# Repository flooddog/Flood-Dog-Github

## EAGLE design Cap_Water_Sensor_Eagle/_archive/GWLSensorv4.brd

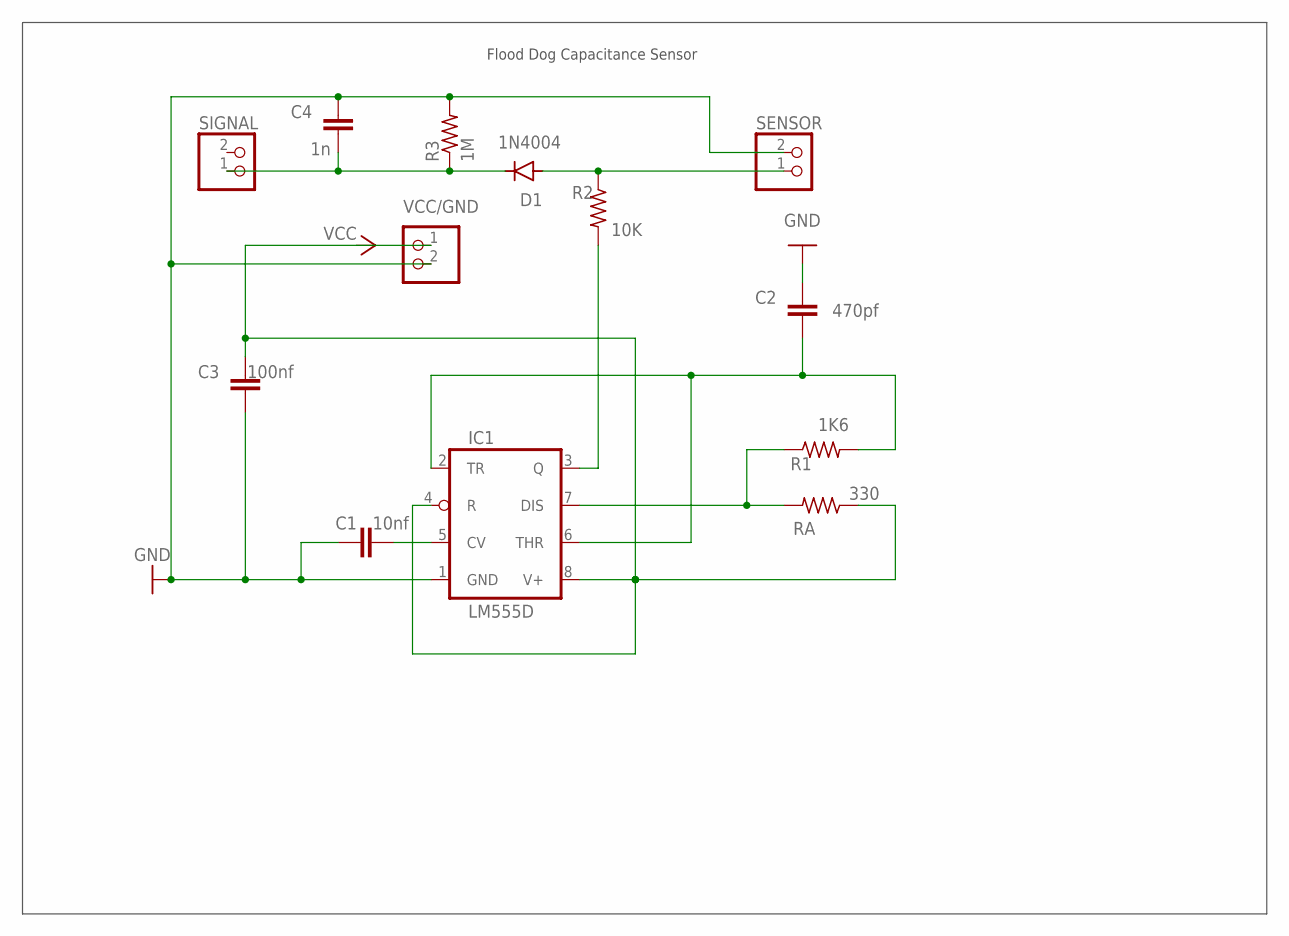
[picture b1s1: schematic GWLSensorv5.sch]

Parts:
C1: 10nf; C0805
C2: 470pf; C0805
C3: 100nf; C0805
C4: 1n; C0805
D1: 1N4004; DO41-10
IC1: LM555D; SO08
R1: 1K6; R0805
R2: 10K; R0805
R3: 1M; R0805
RA: 330; R0805
SENSOR: JST_2PIN-SMT; JST-PH-2-SMT
SIGNAL: JST_2PIN-SMT; JST-PH-2-SMT
VCC/GND: JST_2PIN-SMT; JST-PH-2-SMT

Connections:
GND: C1.1, C2.2, C3.1, C4.2, IC1.1 (GND), R3.2, SENSOR.2 (1), VCC/GND.2 (1)
unnamed: C4.1, D1.C, R3.1, SIGNAL.1 (2)
unnamed: IC1.7 (DIS), R1.1, RA.2
unnamed: C2.1, IC1.2 (TR), IC1.6 (THR), R1.2
unnamed: C1.2, IC1.5 (CV)
unnamed: D1.A, R2.1, SENSOR.1 (2)
unnamed: IC1.3 (Q), R2.2
VCC: C3.2, IC1.4 (R), IC1.8 (V+), RA.1, VCC/GND.1 (2)

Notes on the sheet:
Flood Dog Capacitance Sensor

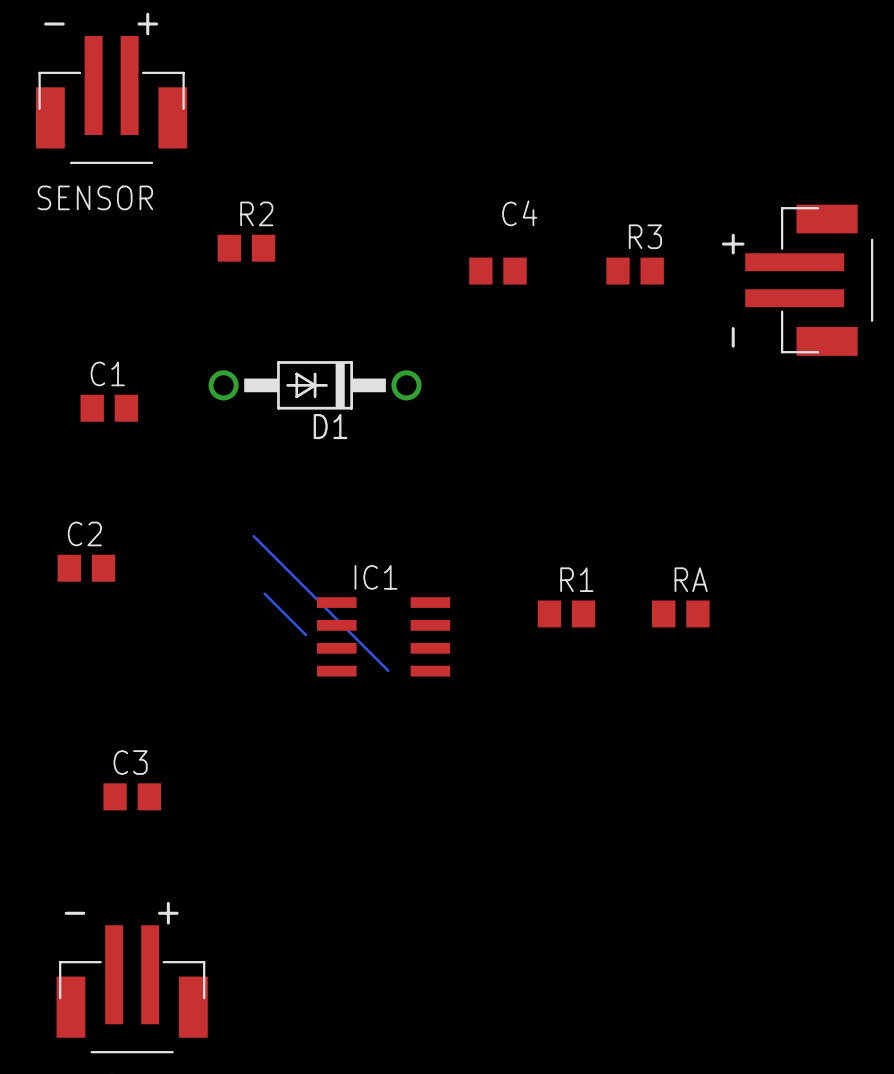
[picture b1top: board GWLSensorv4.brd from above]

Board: 2 copper layers, 13 parts (0 on the bottom side), 8 nets.

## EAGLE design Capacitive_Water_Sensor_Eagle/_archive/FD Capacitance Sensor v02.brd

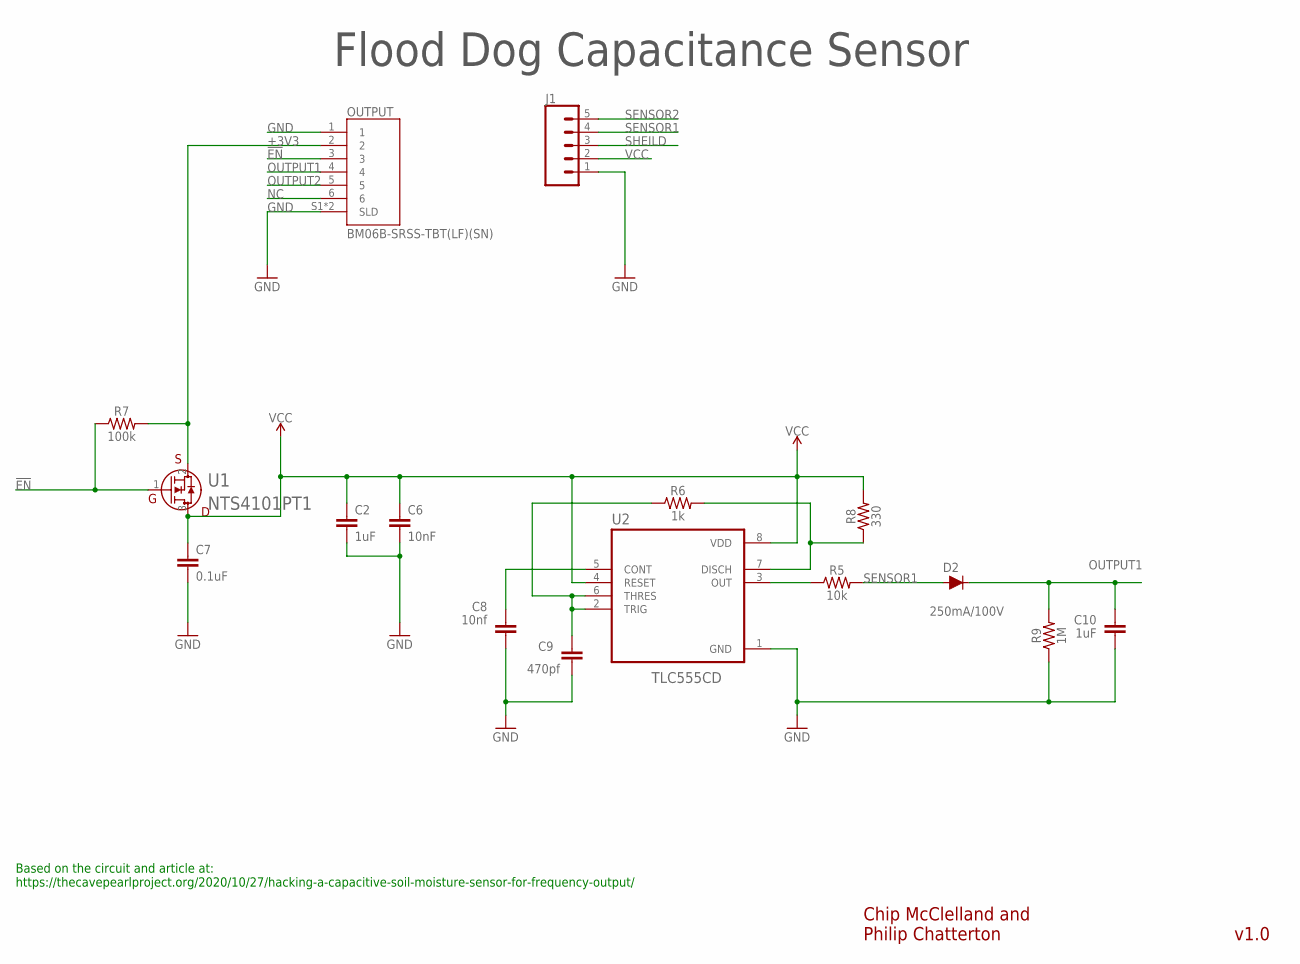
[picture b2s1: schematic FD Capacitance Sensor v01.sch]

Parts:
C2: 1uF; 0805@1
C6: 10nF; 0805@1
C7: 0.1uF; 0805@1
C8: 10nf; C0805
C9: 470pf; C0805
C10: 1uF; C0805
D2: 250mA/100V; SOD-323
J1: CONN_05SCREW; SCREWTERMINAL-3.5MM-5
OUTPUT: BM06B-SRSS-TBT(LF)(SN); JST_BM06B-SRSS-TB(LF)(SN)
R5: 10k; 0805
R6: 1k; 0805
R7: 100k; 0805; MPN MF-RES-0805-100K
R8: 330; 0805
R9: 1M; 0805
U1: NTS4101PT1; SOT_101PT1_ONS
U2: TLC555CD; SOIC127P599X175-8N

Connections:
!EN: OUTPUT.3, R7.1, U1.1 (G)
+3V3: OUTPUT.2, R7.2, U1.2 (S)
GND: C2.2, C6.2, C7.2, C8.1, C9.1, C10.1, J1.1, OUTPUT.1, OUTPUT.S1 (SLD), OUTPUT.S2 (SLD), R9.1, U2.1 (GND)
unnamed: C8.2, U2.5 (CONT)
unnamed: R5.1, U2.3 (OUT)
unnamed: C9.2, R6.1, U2.2 (TRIG), U2.6 (THRES)
unnamed: R6.2, R8.1, U2.7 (DISCH)
NC: OUTPUT.6
OUTPUT1: C10.2, D2.C, OUTPUT.4, R9.2
OUTPUT2: OUTPUT.5
SENSOR1: D2.A, J1.4, R5.2
SENSOR2: J1.5
SHEILD: J1.3
VCC: C2.1, C6.1, C7.1, J1.2, R8.2, U1.3 (D), U2.4 (RESET), U2.8 (VDD)

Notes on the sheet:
Flood Dog Capacitance Sensor
v1.0
Chip McClelland and Philip Chatterton
Based on the circuit and article at: https://thecavepearlproject.org/2020/10/27/hacking-a-capacitive-soil-moisture-sensor-for-frequency-output/

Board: 2 copper layers, 17 parts (0 on the bottom side), 10 nets, no tracks yet.

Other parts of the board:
FRAME1: FRAME-LETTERNO_PACKAGE; DUMMY

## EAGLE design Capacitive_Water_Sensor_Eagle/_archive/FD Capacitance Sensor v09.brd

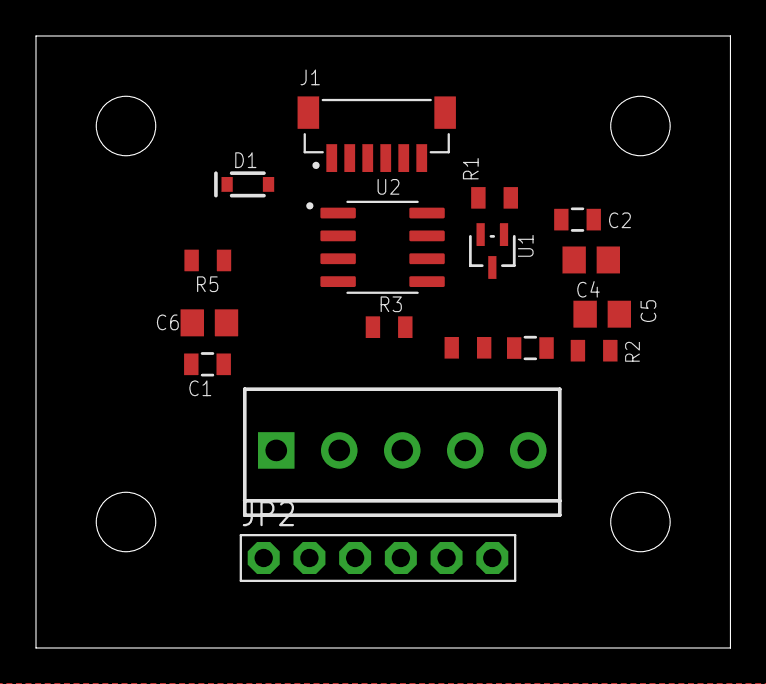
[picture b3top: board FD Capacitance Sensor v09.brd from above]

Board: 2 copper layers, 38.6 x 34.0 mm, 21 parts (0 on the bottom side), 10 nets, no tracks yet.

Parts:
C1: 0.1uF; 0805@1
C2: 1uF; 0805@1
C3: 10nF; 0805@1
C4: 10nf; C0805
C5: 470pf; C0805
C6: 1uF; C0805
D1: 250mA/100V; SOD-323
J1: BM06B-SRSS-TBT(LF)(SN); JST_BM06B-SRSS-TB(LF)(SN)
J2: SCREWTERMINAL-3.5MM-5
JP2: 1X06-BIG
R1: 100k; 0805
R2: 1k; 0805
R3: 10k; 0805
R4: 330; 0805
R5: 1M; 0805
U1: NTS4101PT1; SOT_101PT1_ONS
U2: TLC555CD; SOIC127P599X175-8N
U$1, U$2, U$3, U$4: STAND-OFF

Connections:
!EN: J1.3, R1.1, U1.1
+3V3: J1.2, R1.2, U1.2
GND: C1.2, C2.2, C3.2, C4.1, C5.1, C6.1, J1.1, J1.S1, J1.S2, J2.1, JP2.1, R5.1, U2.1
unnamed: C4.2, U2.5
unnamed: R3.1, U2.3
unnamed: C5.2, R2.1, U2.2, U2.6
unnamed: R2.2, R4.1, U2.7
OUTPUT1: C6.2, D1.C, J1.4, R5.2
SENSOR1: D1.A, J2.4, R3.2
VCC: C1.1, C2.1, C3.1, J2.2, R4.2, U1.3, U2.4, U2.8

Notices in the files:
parts and their libraries:
SparkFun-Connectors: Licensing: Creative Commons ShareAlike 4.0 International - https://creativecommons.org/licenses/by-sa/4.0
